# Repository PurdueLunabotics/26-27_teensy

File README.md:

# Teensy Board

The breakout board for the teensy. Connects all the various sensors into one contained place.

Will use a teensy 4.1

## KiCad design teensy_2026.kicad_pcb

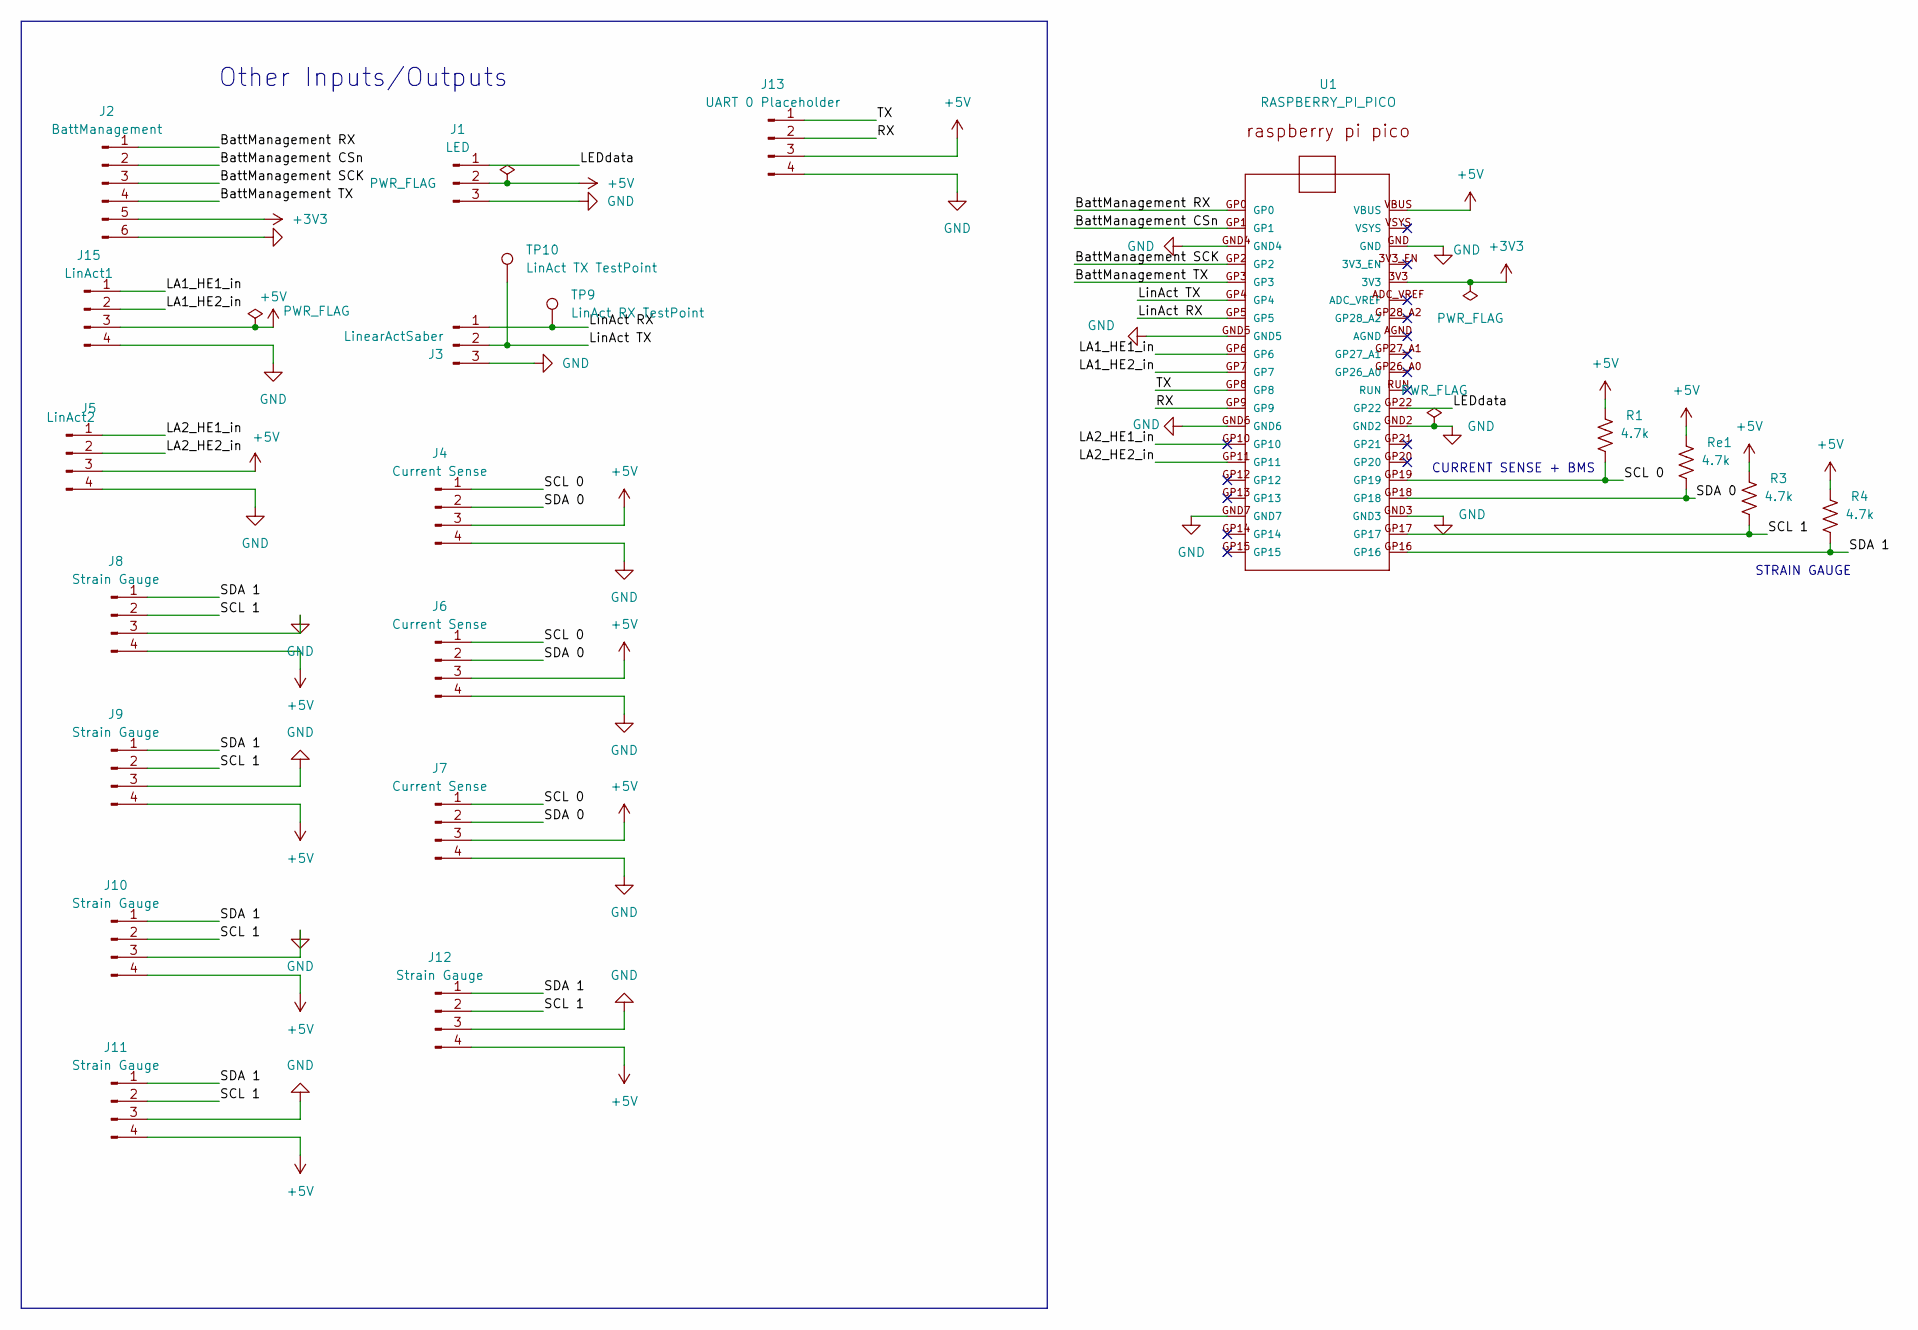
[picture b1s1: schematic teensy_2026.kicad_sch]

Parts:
J1: LED; JST_XH_B3B-XH-A_1x03_P2.50mm_Vertical
J2: BattManagement; JST_XH_B6B-XH-A_1x06_P2.50mm_Vertical
J3: LinearActSaber; JST_XH_B3B-XH-A_1x03_P2.50mm_Vertical
J4, J6, J7: Current Sense; JST_XH_B4B-XH-A_1x04_P2.50mm_Vertical
J5: LinAct2; JST_XH_B4B-XH-A_1x04_P2.50mm_Vertical
J8, J9, J10, J11, J12: Strain Gauge; JST_XH_B4B-XH-A_1x04_P2.50mm_Vertical
J13: UART 0 Placeholder; JST_XH_B4B-XH-A_1x04_P2.50mm_Vertical
J15: LinAct1; JST_XH_B4B-XH-A_1x04_P2.50mm_Vertical
R1, R3, R4: 4.7k; R_Axial_DIN0411_L9.9mm_D3.6mm_P12.70mm_Horizontal
Re1: 4.7k; R_Axial_DIN0411_L9.9mm_D3.6mm_P12.70mm_Horizontal
TP9: LinAct RX TestPoint; SolderWire-0.75sqmm_1x01_D1.25mm_OD2.3mm
TP10: LinAct TX TestPoint; SolderWire-0.75sqmm_1x01_D1.25mm_OD2.3mm
U1: RASPBERRY_PI_PICO

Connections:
+3V3: J2.5, U1.3V3
+5V: J1.2, J4.3, J5.3, J6.3, J7.3, J8.4, J9.4, J10.4, J11.4, J12.4, J13.3, J15.3, R1.1, R3.1, R4.1, Re1.1, U1.VBUS
/BattManagement CSn: J2.2, U1.GP1
/BattManagement RX: J2.1, U1.GP0
/BattManagement SCK: J2.3, U1.GP2
/BattManagement TX: J2.4, U1.GP3
/LA1_HE1_in: J15.1, U1.GP6
/LA1_HE2_in: J15.2, U1.GP7
/LA2_HE1_in: J5.1, U1.GP10
/LA2_HE2_in: J5.2, U1.GP11
/LEDdata: J1.1, U1.GP22
/LinAct RX: J3.1, TP9.1, U1.GP5
/LinAct TX: J3.2, TP10.1, U1.GP4
/RX: J13.2, U1.GP9
/SCL 0: J4.1, J6.1, J7.1, R1.2, U1.GP19
/SCL 1: J8.2, J9.2, J10.2, J11.2, J12.2, R3.2, U1.GP17
/SDA 0: J4.2, J6.2, J7.2, Re1.2, U1.GP18
/SDA 1: J8.1, J9.1, J10.1, J11.1, J12.1, R4.2, U1.GP16
/TX: J13.1, U1.GP8
GND: J1.3, J2.6, J3.3, J4.4, J5.4, J6.4, J7.4, J8.3, J9.3, J10.3, J11.3, J12.3, J13.4, J15.4, U1.GND, U1.GND2, U1.GND3, U1.GND4, U1.GND5, U1.GND6, U1.GND7

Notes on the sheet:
CURRENT SENSE + BMS
STRAIN GAUGE
Other Inputs/Outputs

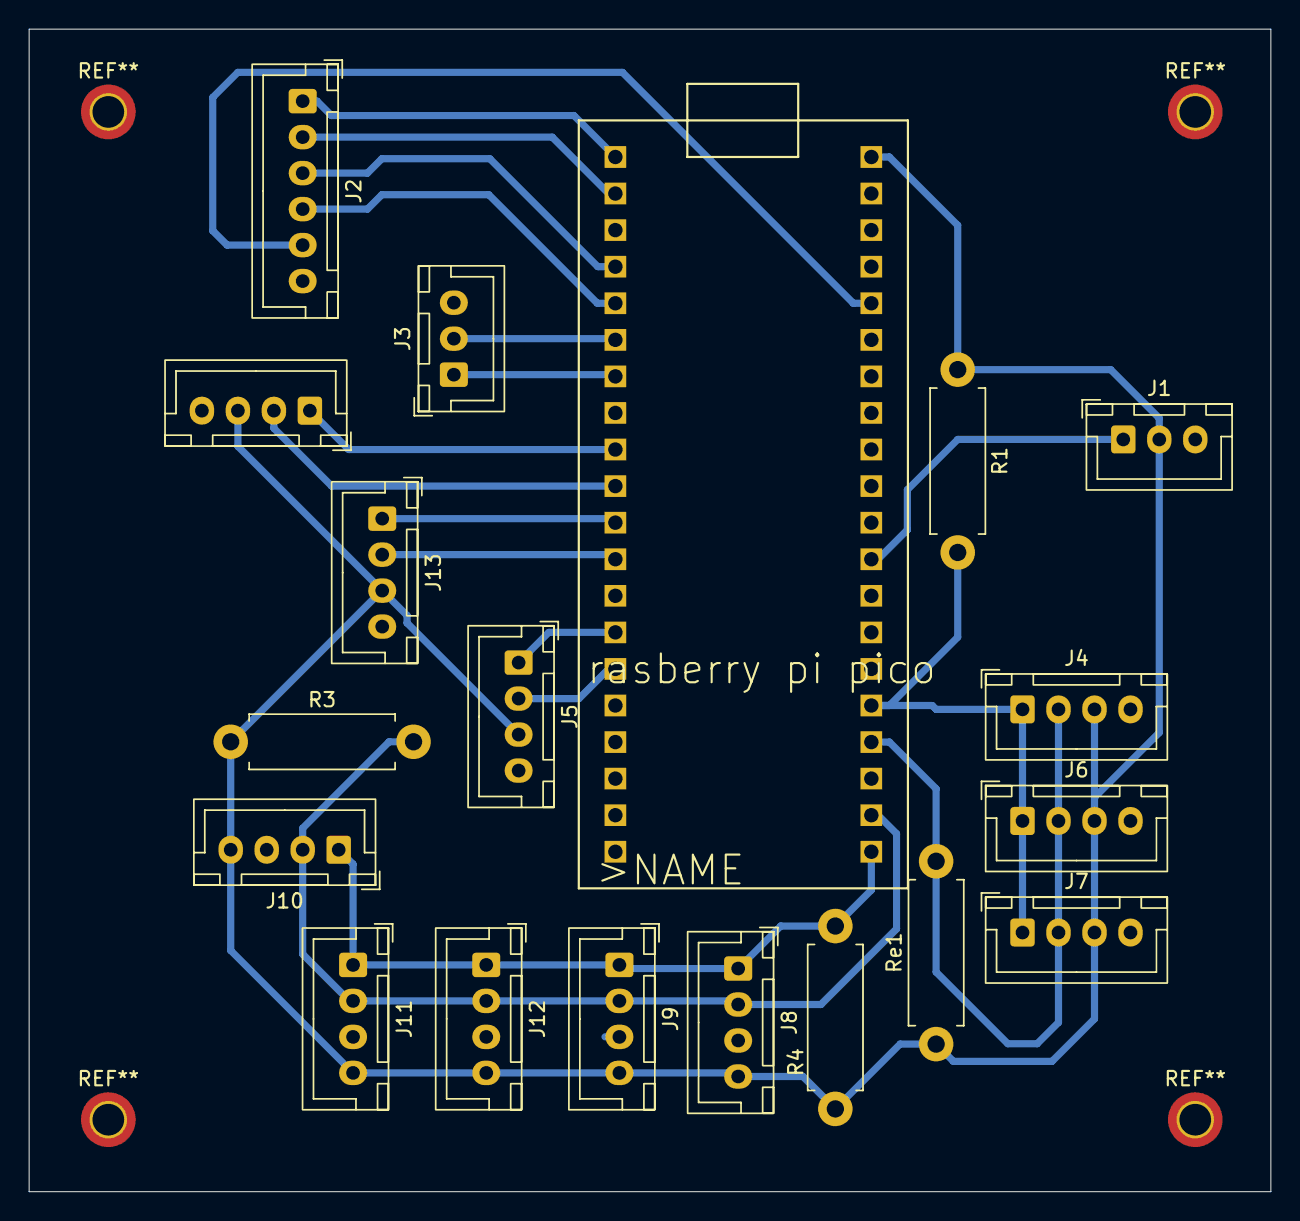
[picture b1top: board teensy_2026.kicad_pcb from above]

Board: 2 copper layers, 86.2 x 80.8 mm, 19 parts (0 on the bottom side), 20 nets.
